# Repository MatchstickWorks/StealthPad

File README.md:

# StealthPad
 Rebuild of the Steelseries Merc Stealth macro-pad section using an RP2040 chip

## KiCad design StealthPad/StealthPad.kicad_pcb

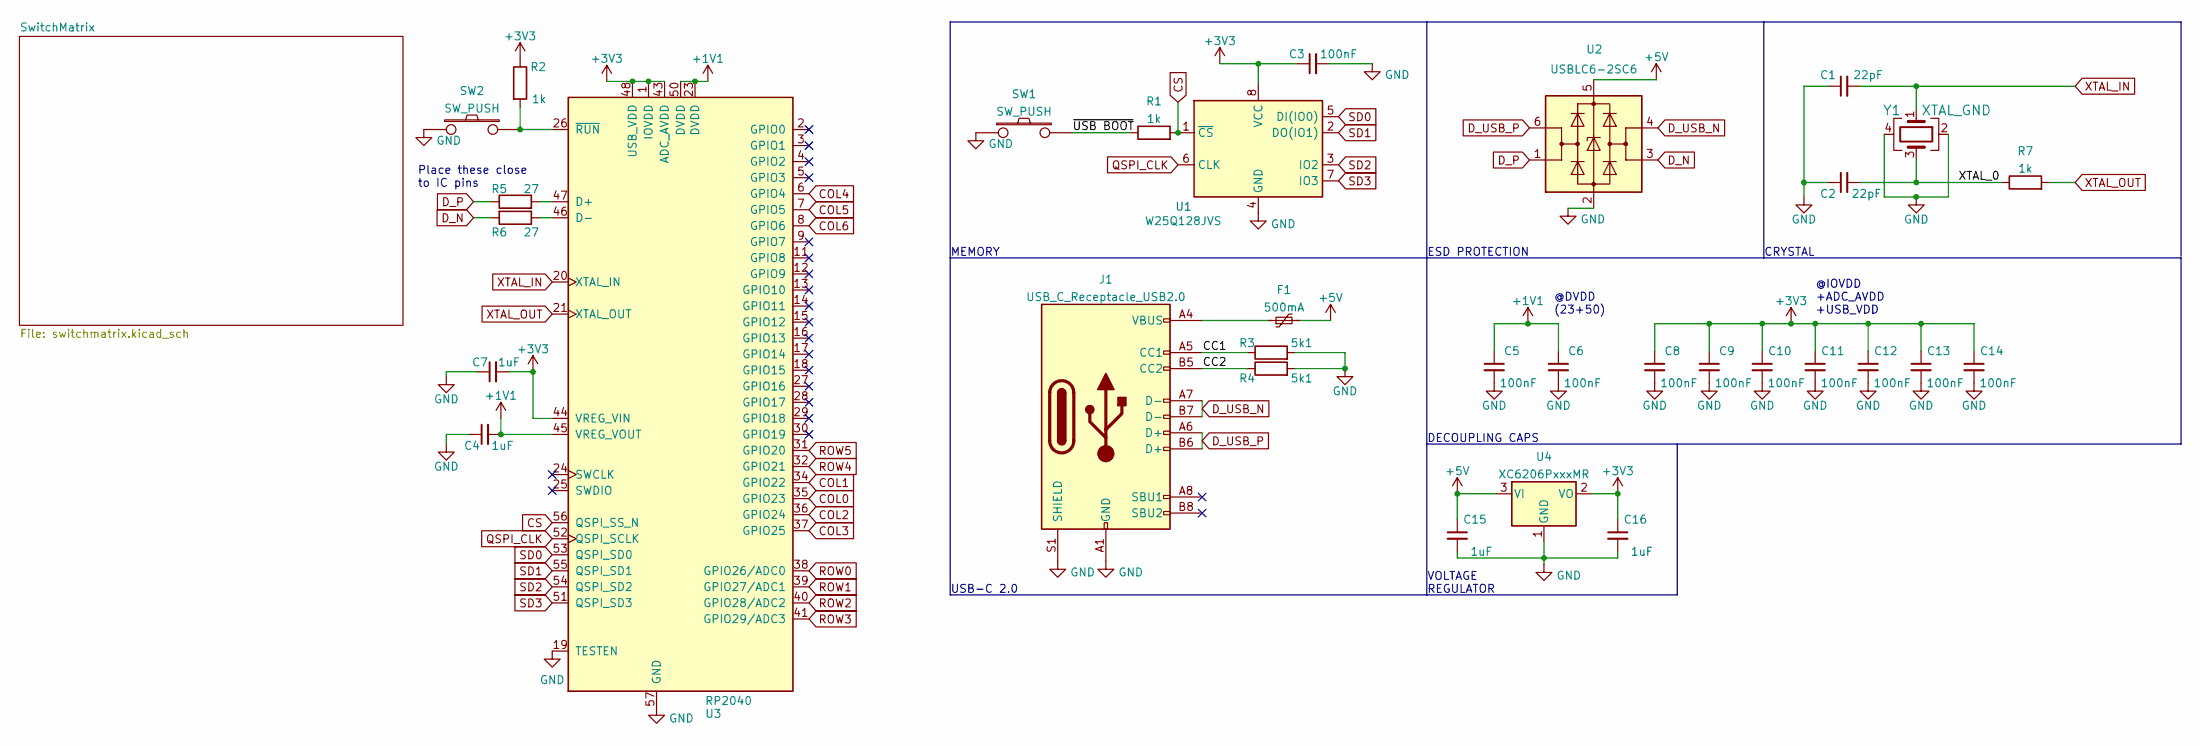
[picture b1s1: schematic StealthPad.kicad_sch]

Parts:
C1, C2: 22pF; C_0603_1608Metric; MPN C1653
C3, C5, C6, C8, C9, C10, C11, C12, C13, C14: 100nF; C_0603_1608Metric; MPN C14663
C4, C7, C15, C16: 1uF; C_0603_1608Metric; MPN C15849
F1: 500mA; Fuse_1206_3216Metric; MPN C70076
J1: USB_C_Receptacle_USB2.0; USB_C_Receptacle_HRO_TYPE-C-31-M-12; MPN C165948
R1, R2, R7: 1k; R_0603_1608Metric; MPN C21190
R3, R4: 5k1; R_0603_1608Metric; MPN C23186
R5, R6: 27; R_0603_1608Metric; MPN C25190
SW1, SW2: SW_PUSH; SW_TACTILE_SMD; MPN C318884
U1: W25Q128JVS; SOIC-8_5.23x5.23mm_P1.27mm; MPN C97521
U2: USBLC6-2SC6; SOT-23-6; MPN C85364
U3: RP2040; RP2040-QFN-56; MPN C2040
U4: XC6206PxxxMR; SOT-23; MPN C5446
Y1: XTAL_GND; Crystal_SMD_3225-4Pin_3.2x2.5mm; MPN C13738

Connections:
+1V1: C4.2, C5.1, C6.1, U3.23 (DVDD), U3.45 (VREG_VOUT), U3.50 (DVDD)
+3V3: C3.1, C7.2, C8.1, C9.1, C10.1, C11.1, C12.1, C13.1, C14.1, C16.1, R2.1, U1.8 (VCC), U3.1 (IOVDD), U3.10 (IOVDD), U3.22 (IOVDD), U3.33 (IOVDD), U3.42 (IOVDD), U3.43 (ADC_AVDD), U3.44 (VREG_VIN), U3.48 (USB_VDD), U3.49 (IOVDD), U4.2 (VO)
+5V: C15.1, F1.2, U2.5 (VBUS), U4.3 (VI)
/CC1: J1.A5 (CC1), R3.1
/CC2: J1.B5 (CC2), R4.1
/XTAL_0: C2.2, R7.1, Y1.3
/~USB BOOT: R1.1, SW1.2
COL0: U3.35 (GPIO23); also elsewhere on the board
COL1: U3.34 (GPIO22); also elsewhere on the board
COL2: U3.36 (GPIO24); also elsewhere on the board
COL3: U3.37 (GPIO25); also elsewhere on the board
COL4: U3.6 (GPIO4); also elsewhere on the board
COL5: U3.7 (GPIO5); also elsewhere on the board
COL6: U3.8 (GPIO6); also elsewhere on the board
CS: R1.2, U1.1 (~CS), U3.56 (QSPI_SS_N)
D_N: R6.2, U2.3 (I/O2)
D_P: R5.1, U2.1 (I/O1)
D_USB_N: J1.A7 (D-), J1.B7 (D-), U2.4 (I/O2)
D_USB_P: J1.A6 (D+), J1.B6 (D+), U2.6 (I/O1)
GND: C1.1, C2.1, C3.2, C4.1, C5.2, C6.2, C7.1, C8.2, C9.2, C10.2, C11.2, C12.2, C13.2, C14.2, C15.2, C16.2, J1.A1 (GND), J1.A12 (GND), J1.B1 (GND), J1.B12 (GND), J1.S1 (SHIELD), R3.2, R4.2, SW1.1, SW2.1, U1.4 (GND), U2.2 (GND), U3.19 (TESTEN), U3.57 (GND), U4.1 (GND), Y1.2, Y1.4
unnamed: F1.1, J1.A4 (VBUS), J1.A9 (VBUS), J1.B4 (VBUS), J1.B9 (VBUS)
unnamed: R2.2, SW2.2, U3.26 (~RUN)
unnamed: R5.2, U3.47 (D+)
unnamed: R6.1, U3.46 (D-)
QSPI_CLK: U1.6 (CLK), U3.52 (QSPI_SCLK)
ROW0: U3.38 (GPIO26/ADC0); also elsewhere on the board
ROW1: U3.39 (GPIO27/ADC1); also elsewhere on the board
ROW2: U3.40 (GPIO28/ADC2); also elsewhere on the board
ROW3: U3.41 (GPIO29/ADC3); also elsewhere on the board
ROW4: U3.32 (GPIO21); also elsewhere on the board
ROW5: U3.31 (GPIO20); also elsewhere on the board
SD0: U1.5 (DI(IO0)), U3.53 (QSPI_SD0)
SD1: U1.2 (DO(IO1)), U3.55 (QSPI_SD1)
SD2: U1.3 (IO2), U3.54 (QSPI_SD2)
SD3: U1.7 (IO3), U3.51 (QSPI_SD3)
XTAL_IN: C1.2, U3.20 (XTAL_IN), Y1.1
XTAL_OUT: R7.2, U3.21 (XTAL_OUT)

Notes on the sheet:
VOLTAGE REGULATOR
USB-C 2.0
ESD PROTECTION
CRYSTAL
DECOUPLING CAPS
@DVDD (23+50)
Place these close to IC pins
@IOVDD +ADC_AVDD +USB_VDD
MEMORY

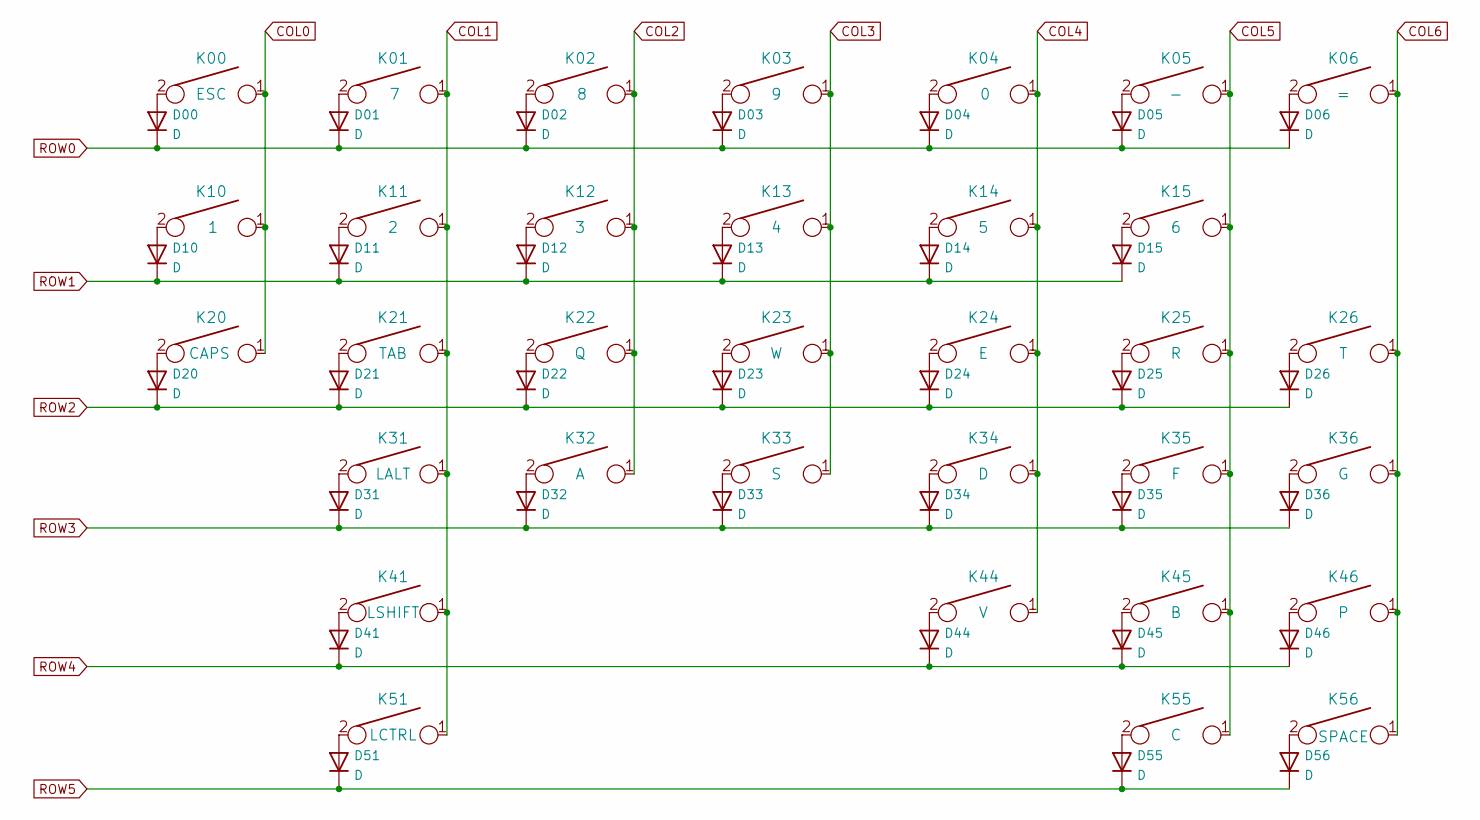
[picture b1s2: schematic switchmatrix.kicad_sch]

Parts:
D00, D01, D02, D03, D04, D05, D06, D10, D11, D12, D13, D14, D15, D20, D21, D22, D23, D24, D25, D26, D31, D32, D33, D34, D35, D36, D41, D44, D45, D46, D51, D55, D56: D; D_SOD-123; MPN C81598
K00: ESC; Kailh_MX_Socket; MPN C5156480
K01: 7; Kailh_MX_Socket; MPN C5156480
K02: 8; Kailh_MX_Socket; MPN C5156480
K03: 9; Kailh_MX_Socket; MPN C5156480
K04: 0; Kailh_MX_Socket; MPN C5156480
K05: -; Kailh_MX_Socket; MPN C5156480
K06: =; Kailh_MX_Socket; MPN C5156480
K10: 1; Kailh_MX_Socket; MPN C5156480
K11: 2; Kailh_MX_Socket; MPN C5156480
K12: 3; Kailh_MX_Socket; MPN C5156480
K13: 4; Kailh_MX_Socket; MPN C5156480
K14: 5; Kailh_MX_Socket; MPN C5156480
K15: 6; Kailh_MX_Socket; MPN C5156480
K20: CAPS; Kailh_MX_Socket; MPN C5156480
K21: TAB; Kailh_MX_Socket; MPN C5156480
K22: Q; Kailh_MX_Socket; MPN C5156480
K23: W; Kailh_MX_Socket; MPN C5156480
K24: E; Kailh_MX_Socket; MPN C5156480
K25: R; Kailh_MX_Socket; MPN C5156480
K26: T; Kailh_MX_Socket; MPN C5156480
K31: LALT; Kailh_MX_Socket; MPN C5156480
K32: A; Kailh_MX_Socket; MPN C5156480
K33: S; Kailh_MX_Socket; MPN C5156480
K34: D; Kailh_MX_Socket; MPN C5156480
K35: F; Kailh_MX_Socket; MPN C5156480
K36: G; Kailh_MX_Socket; MPN C5156480
K41: LSHIFT; Kailh_MX_Socket; MPN C5156480
K44: V; Kailh_MX_Socket; MPN C5156480
K45: B; Kailh_MX_Socket; MPN C5156480
K46: P; Kailh_MX_Socket; MPN C5156480
K51: LCTRL; Kailh_MX_Socket; MPN C5156480
K55: C; Kailh_MX_Socket; MPN C5156480
K56: SPACE; Kailh_MX_Socket; MPN C5156480

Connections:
COL0: K00.1, K10.1, K20.1; also elsewhere on the board
COL1: K01.1, K11.1, K21.1, K31.1, K41.1, K51.1; also elsewhere on the board
COL2: K02.1, K12.1, K22.1, K32.1; also elsewhere on the board
COL3: K03.1, K13.1, K23.1, K33.1; also elsewhere on the board
COL4: K04.1, K14.1, K24.1, K34.1, K44.1; also elsewhere on the board
COL5: K05.1, K15.1, K25.1, K35.1, K45.1, K55.1; also elsewhere on the board
COL6: K06.1, K26.1, K36.1, K46.1, K56.1; also elsewhere on the board
unnamed: D00.2 (A), K00.2
unnamed: D01.2 (A), K01.2
unnamed: D02.2 (A), K02.2
unnamed: D03.2 (A), K03.2
unnamed: D04.2 (A), K04.2
unnamed: D05.2 (A), K05.2
unnamed: D06.2 (A), K06.2
unnamed: D10.2 (A), K10.2
unnamed: D11.2 (A), K11.2
unnamed: D12.2 (A), K12.2
unnamed: D13.2 (A), K13.2
unnamed: D14.2 (A), K14.2
unnamed: D15.2 (A), K15.2
unnamed: D20.2 (A), K20.2
unnamed: D21.2 (A), K21.2
unnamed: D22.2 (A), K22.2
unnamed: D23.2 (A), K23.2
unnamed: D24.2 (A), K24.2
unnamed: D25.2 (A), K25.2
unnamed: D26.2 (A), K26.2
unnamed: D31.2 (A), K31.2
unnamed: D32.2 (A), K32.2
unnamed: D33.2 (A), K33.2
unnamed: D34.2 (A), K34.2
unnamed: D35.2 (A), K35.2
unnamed: D36.2 (A), K36.2
unnamed: D41.2 (A), K41.2
unnamed: D44.2 (A), K44.2
unnamed: D45.2 (A), K45.2
unnamed: D46.2 (A), K46.2
unnamed: D51.2 (A), K51.2
unnamed: D55.2 (A), K55.2
unnamed: D56.2 (A), K56.2
ROW0: D00.1 (K), D01.1 (K), D02.1 (K), D03.1 (K), D04.1 (K), D05.1 (K), D06.1 (K); also elsewhere on the board
ROW1: D10.1 (K), D11.1 (K), D12.1 (K), D13.1 (K), D14.1 (K), D15.1 (K); also elsewhere on the board
ROW2: D20.1 (K), D21.1 (K), D22.1 (K), D23.1 (K), D24.1 (K), D25.1 (K), D26.1 (K); also elsewhere on the board
ROW3: D31.1 (K), D32.1 (K), D33.1 (K), D34.1 (K), D35.1 (K), D36.1 (K); also elsewhere on the board
ROW4: D41.1 (K), D44.1 (K), D45.1 (K), D46.1 (K); also elsewhere on the board
ROW5: D51.1 (K), D55.1 (K), D56.1 (K); also elsewhere on the board

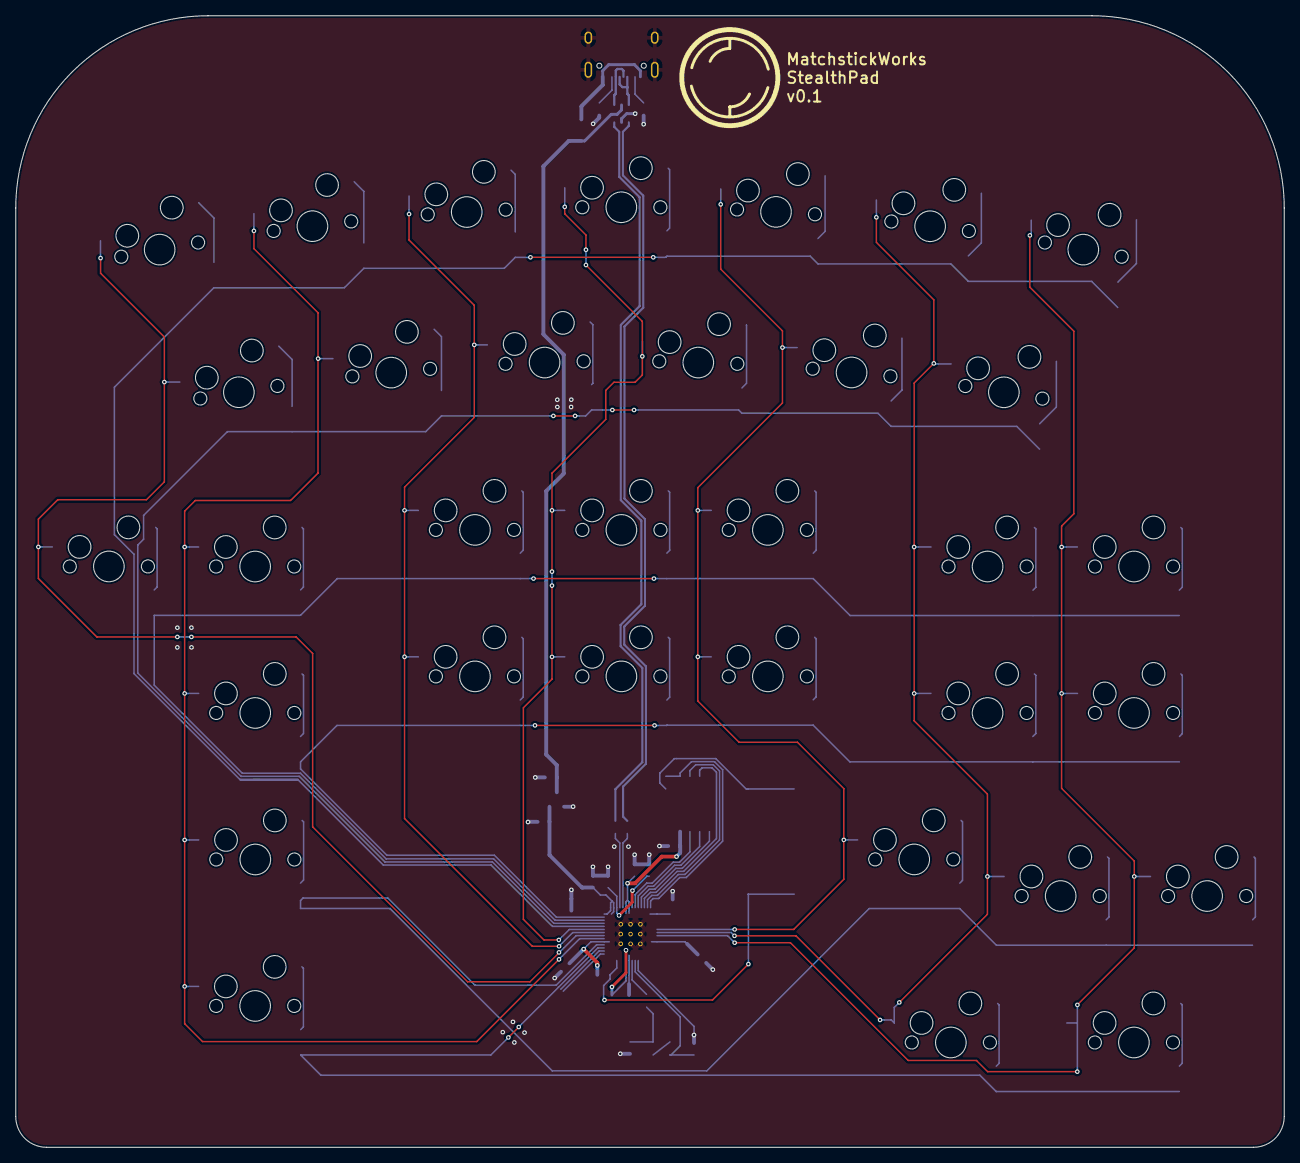
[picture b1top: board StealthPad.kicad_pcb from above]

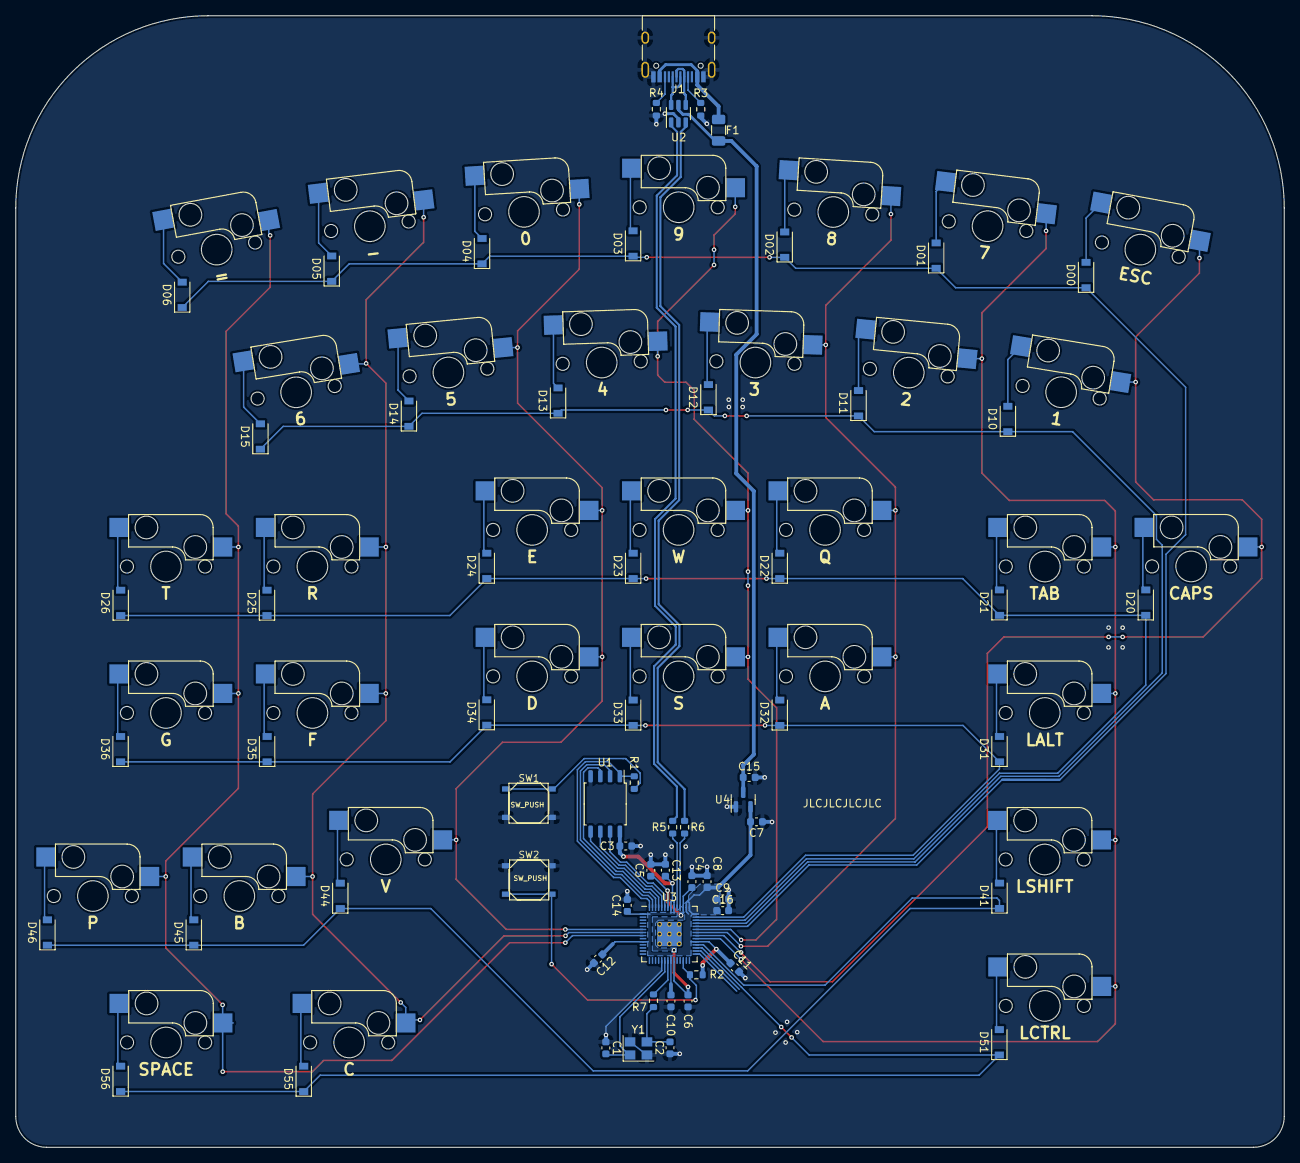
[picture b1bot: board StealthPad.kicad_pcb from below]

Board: 2 copper layers, 165.0 x 147.2 mm, 98 parts (98 on the bottom side), 70 nets.

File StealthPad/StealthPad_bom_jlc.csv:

"Comment","Designator","Footprint","LCSC Part #"
"22pF","C1,C2","C_0603_1608Metric","C1653"
"100nF","C3,C5,C6,C8,C9,C10,C11,C12,C13,C14","C_0603_1608Metric","C14663"
"1uF","C4,C7,C15,C16","C_0603_1608Metric","C15849"
"D","D00,D01,D02,D03,D04,D05,D06,D10,D11,D12,D13,D14,D15,D20,D21,D22,D23,D24,D25,D26,D31,D32,D33,D34,D35,D36,D41,D44,D45,D46,D51,D55,D56","D_SOD-123","C81598"
"500mA","F1","Fuse_1206_3216Metric","C70076"
"USB_C_Receptacle_USB2.0","J1","USB_C_Receptacle_HRO_TYPE-C-31-M-12","C165948"
"ESC","K00","Kailh_MX_Socket","C5156480"
"7","K01","Kailh_MX_Socket","C5156480"
"8","K02","Kailh_MX_Socket","C5156480"
"9","K03","Kailh_MX_Socket","C5156480"
"0","K04","Kailh_MX_Socket","C5156480"
"-","K05","Kailh_MX_Socket","C5156480"
"=","K06","Kailh_MX_Socket","C5156480"
"1","K10","Kailh_MX_Socket","C5156480"
"2","K11","Kailh_MX_Socket","C5156480"
"3","K12","Kailh_MX_Socket","C5156480"
"4","K13","Kailh_MX_Socket","C5156480"
"5","K14","Kailh_MX_Socket","C5156480"
"6","K15","Kailh_MX_Socket","C5156480"
"CAPS","K20","Kailh_MX_Socket","C5156480"
"TAB","K21","Kailh_MX_Socket","C5156480"
"Q","K22","Kailh_MX_Socket","C5156480"
"W","K23","Kailh_MX_Socket","C5156480"
"E","K24","Kailh_MX_Socket","C5156480"
"R","K25","Kailh_MX_Socket","C5156480"
"T","K26","Kailh_MX_Socket","C5156480"
"LALT","K31","Kailh_MX_Socket","C5156480"
"A","K32","Kailh_MX_Socket","C5156480"
"S","K33","Kailh_MX_Socket","C5156480"
"D","K34","Kailh_MX_Socket","C5156480"
"F","K35","Kailh_MX_Socket","C5156480"
"G","K36","Kailh_MX_Socket","C5156480"
"LSHIFT","K41","Kailh_MX_Socket","C5156480"
"V","K44","Kailh_MX_Socket","C5156480"
"B","K45","Kailh_MX_Socket","C5156480"
"P","K46","Kailh_MX_Socket","C5156480"
"LCTRL","K51","Kailh_MX_Socket","C5156480"
"C","K55","Kailh_MX_Socket","C5156480"
"SPACE","K56","Kailh_MX_Socket","C5156480"
"1k","R1,R2,R7","R_0603_1608Metric","C21190"
"5k1","R3,R4","R_0603_1608Metric","C23186"
"27","R5,R6","R_0603_1608Metric","C25190"
"SW_PUSH","SW1,SW2","SW_TACTILE_SMD","C318884"
"W25Q128JVS","U1","SOIC-8_5.23x5.23mm_P1.27mm","C97521"
"USBLC6-2SC6","U2","SOT-23-6","C85364"
"RP2040","U3","RP2040-QFN-56","C2040"
"XC6206PxxxMR","U4","SOT-23","C5446"
"XTAL_GND","Y1","Crystal_SMD_3225-4Pin_3.2x2.5mm","C13738"

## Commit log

2022-06-26 Finalize schematic layout
2022-06-26 Schematic finished, started on layout
2022-08-13 Just a lil updatin'
2022-10-11 WIP Updates
2022-10-11 Ordered JLC Protoparts
2022-10-17 Gerber uploads
2025-01-28 Updating?
